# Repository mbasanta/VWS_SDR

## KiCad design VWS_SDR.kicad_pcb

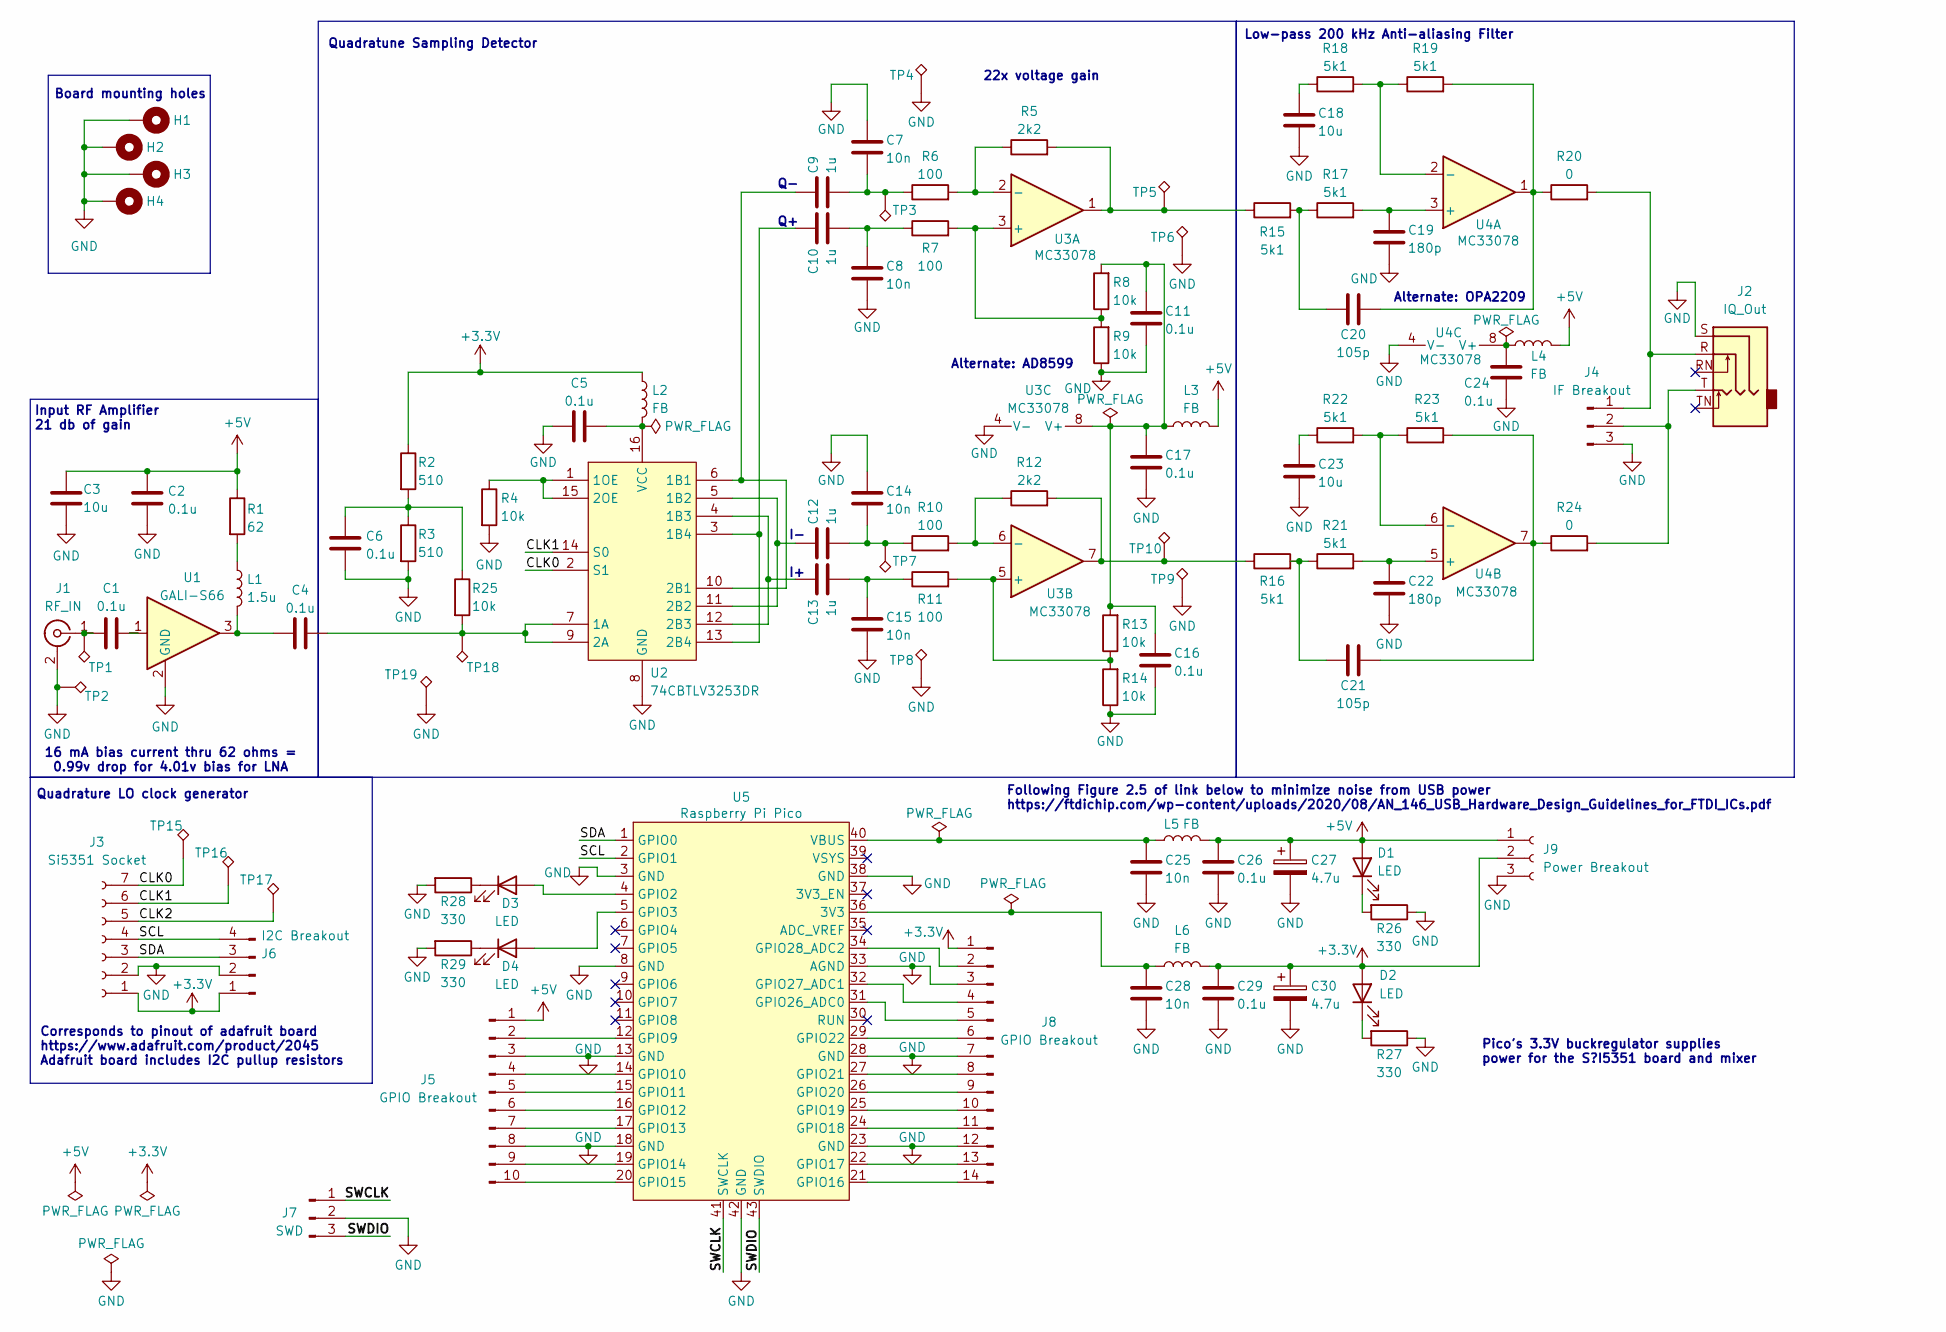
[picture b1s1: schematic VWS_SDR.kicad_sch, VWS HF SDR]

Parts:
C1, C2, C4, C5, C6, C11, C16, C17, C24, C26, C29: 0.1u; C_1206_3216Metric_Pad1.33x1.80mm_HandSolder; Digikey PN 399-C1206C104K5RACTUCT-ND
C3, C18, C23: 10u; C_1206_3216Metric_Pad1.33x1.80mm_HandSolder; Digikey PN 399-C1206C106K4RACTUCT-ND
C7, C8, C14, C15, C25, C28: 10n; C_1206_3216Metric_Pad1.33x1.80mm_HandSolder; Digikey PN 399-C1206C103K5RACTUCT-ND
C9, C10, C12, C13: 1u; C_1206_3216Metric_Pad1.33x1.80mm_HandSolder; Digikey PN 399-C1206C105K3RACTUCT-ND
C19, C22: 180p; C_1206_3216Metric_Pad1.33x1.80mm_HandSolder; Digikey PN 311-4412-1-ND
C20, C21: 105p; C_1206_3216Metric_Pad1.33x1.80mm_HandSolder; Digikey PN 399-17651-1-ND
C27, C30: 4.7u; CP_Radial_D5.0mm_P2.00mm; Digikey PN 399-ESW475M025AC3AA-ND
D1, D2: LED; LED_1206_3216Metric_Pad1.42x1.75mm_HandSolder; Digikey PN 732-4988-1-ND
D3: LED; LED_1206_3216Metric_Pad1.42x1.75mm_HandSolder; Digikey PN 732-4990-1-ND
D4: LED; LED_1206_3216Metric_Pad1.42x1.75mm_HandSolder; Digikey PN 732-4989-1-ND
H1, H2, H3, H4: MountingHole_Pad; MountingHole_3.2mm_M3_ISO7380_Pad
J1: RF_IN; SMA_Amphenol_901-144_Vertical; Digikey PN 2057-RF2-03E-T-00-50-G-ND
J2: IQ_Out; Jack_3.5mm_CUI_SJ1-3515N_Horizontal; Digikey PN CP1-3515N-ND
J3: Si5351 Socket; Adafruit_Si5351; Digikey PN 1528-1206-ND
J4: IF Breakout; PinHeader_1x03_P2.54mm_Vertical; Digikey PN 2057-RS1-03-G-ND
J5: GPIO Breakout; PinHeader_1x10_P2.54mm_Vertical; Digikey PN 2057-RS1-10-G-ND
J6: I2C Breakout; PinHeader_1x04_P2.54mm_Vertical; Digikey PN 2057-RS1-04-G-ND
J7: SWD; PinHeader_1x03_P2.54mm_Vertical; Digikey PN 2057-RS1-03-G-ND
J8: GPIO Breakout; PinHeader_1x14_P2.54mm_Vertical; Digikey PN 2057-RS1-14-G-ND
J9: Power Breakout; PinHeader_1x03_P2.54mm_Vertical; Digikey PN 2057-RS1-03-G-ND
L1: 1.5u; L_1206_3216Metric_Pad1.42x1.75mm_HandSolder; Digikey PN 541-ILSB1206ER1R5KCT-ND
L2, L3, L4, L5, L6: FB; L_1206_3216Metric_Pad1.42x1.75mm_HandSolder; Digikey PN 1934-1489-1-ND
R1: 62; R_1206_3216Metric_Pad1.30x1.75mm_HandSolder; Digikey PN 311-62ERCT-ND
R2, R3: 510; R_1206_3216Metric_Pad1.30x1.75mm_HandSolder; Digikey PN 311-510ERCT-ND
R4, R8, R9, R13, R14, R25: 10k; R_1206_3216Metric_Pad1.30x1.75mm_HandSolder; Digikey PN 311-10KERCT-ND
R5, R12: 2k2; R_1206_3216Metric_Pad1.30x1.75mm_HandSolder; Digikey PN 311-2.2KERCT-ND
R6, R7, R10, R11: 100; R_1206_3216Metric_Pad1.30x1.75mm_HandSolder; Digikey PN 311-100ERCT-ND
R15, R16, R17, R18, R19, R21, R22, R23: 5k1; R_1206_3216Metric_Pad1.30x1.75mm_HandSolder; Digikey PN 311-5.1KERCT-ND
R20, R24: 0; R_1206_3216Metric_Pad1.30x1.75mm_HandSolder; Digikey PN 311-0.0ERCT-ND
R26, R27, R28, R29: 330; R_1206_3216Metric_Pad1.30x1.75mm_HandSolder; Digikey PN 311-330ERCT-ND
TP1, TP2, TP3, TP4, TP5, TP6, TP7, TP8, TP9, TP10, TP15, TP16, TP17, TP18, TP19: TP1; TestPoint_THTPad_D2.0mm_Drill1.0mm
U1: GALI-S66; SOT-89-3; Digikey PN 3157-GALI-S66+CT-ND
U2: 74CBTLV3253DR; SOIC-16_3.9x9.9mm_P1.27mm; Digikey PN 296-9132-1-ND
U3, U4: MC33078; SOIC-8_3.9x4.9mm_P1.27mm; Digikey PN 497-1952-1-ND
U5: Raspberry Pi Pico; RPi_Pico_SMD_TH; Digikey PN 2648-SC0915CT-ND

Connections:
+3.3V: C29.1, C30.1, D2.2 (A), J3.1, J6.1, J8.1, J9.2, L2.1, L6.2, R2.1
+5V: C2.2, C3.2, C26.1, C27.1, D1.2 (A), J5.1, J9.1, L3.2, L4.2, L5.2, R1.1
/CLK0: J3.7, TP15.1, U2.2 (S1)
/CLK1: J3.6, TP16.1, U2.14 (S0)
/CLK2: J3.5, TP17.1
/SCL: J3.4, J6.4, U5.2 (GPIO1)
/SDA: J3.3, J6.3, U5.1 (GPIO0)
/SWCLK: J7.1, U5.41 (SWCLK)
/SWDIO: J7.3, U5.43 (SWDIO)
GND: C2.1, C3.1, C5.2, C6.2, C7.1, C8.2, C11.2, C14.1, C15.2, C16.2, C17.2, C18.2, C19.2, C22.2, C23.2, C24.2, C25.2, C26.2, C27.2, C28.2, C29.2, C30.2, H1.1, H2.1, H3.1, H4.1, J1.2 (Ext), J2.S, J3.2, J4.3, J5.3, J5.8, J6.2, J7.2, J8.3, J8.7, J8.12, J9.3, R3.2, R4.2, R9.1, R14.1, R26.1, R27.1, R28.2, R29.2, TP2.1, TP4.1, TP6.1, TP8.1, TP9.1, TP19.1, U1.2 (GND), U2.8 (GND), U3.4 (V-), U4.4 (V-), U5.3 (GND), U5.8 (GND), U5.13 (GND), U5.18 (GND), U5.23 (GND), U5.28 (GND), U5.33 (AGND), U5.38 (GND), U5.42 (GND)
unnamed: C1.2, U1.1
unnamed: C4.2, L1.2, U1.3
unnamed: C6.1, R2.2, R3.1, R25.1
unnamed: C7.2, C9.2, R6.1, TP3.1
unnamed: C8.1, C10.2, R7.1
unnamed: C12.2, C14.2, R10.1, TP7.1
unnamed: C13.2, C15.1, R11.1
unnamed: C18.1, R18.1
unnamed: C20.1, R19.2, R20.1, U4.1
unnamed: C20.2, R15.2, R17.1
unnamed: C21.1, R23.2, R24.1, U4.7
unnamed: C21.2, R16.2, R21.1
unnamed: C23.1, R22.1
unnamed: D1.1 (K), R26.2
unnamed: D2.1 (K), R27.2
unnamed: D3.2 (A), U5.4 (GPIO2)
unnamed: D3.1 (K), R28.1
unnamed: D4.2 (A), U5.5 (GPIO3)
unnamed: D4.1 (K), R29.1
unnamed: C1.1, J1.1 (In), TP1.1
unnamed: J2.R, J4.1, R20.2
unnamed: J2.T, J4.2, R24.2
unnamed: J5.2, U5.12 (GPIO9)
unnamed: J5.4, U5.14 (GPIO10)
unnamed: J5.5, U5.15 (GPIO11)
unnamed: J5.6, U5.16 (GPIO12)
unnamed: J5.7, U5.17 (GPIO13)
unnamed: J5.9, U5.19 (GPIO14)
unnamed: J5.10, U5.20 (GPIO15)
unnamed: J8.2, U5.34 (GPIO28_ADC2)
unnamed: J8.4, U5.32 (GPIO27_ADC1)
unnamed: J8.5, U5.31 (GPIO26_ADC0)
unnamed: J8.6, U5.29 (GPIO22)
unnamed: J8.8, U5.27 (GPIO21)
unnamed: J8.9, U5.26 (GPIO20)
unnamed: J8.10, U5.25 (GPIO19)
unnamed: J8.11, U5.24 (GPIO18)
unnamed: J8.13, U5.22 (GPIO17)
unnamed: J8.14, U5.21 (GPIO16)
unnamed: L1.1, R1.2
unnamed: R12.2, R16.1, TP10.1, U3.7
unnamed: R5.2, R15.1, TP5.1, U3.1
unnamed: C4.1, R25.2, TP18.1, U2.7 (1A), U2.9 (2A)
unnamed: C9.1, U2.6 (1B1), U2.10 (2B1)
unnamed: C12.1, U2.5 (1B2), U2.11 (2B2)
unnamed: C13.1, U2.4 (1B3), U2.12 (2B3)
unnamed: C10.1, U2.3 (1B4), U2.13 (2B4)
unnamed: R4.1, U2.1 (1OE), U2.15 (2OE)
unnamed: C5.1, L2.2, U2.16 (VCC)
unnamed: R7.2, R8.1, R9.2, U3.3 (+)
unnamed: R5.1, R6.2, U3.2 (-)
unnamed: R11.2, R13.1, R14.2, U3.5 (+)
unnamed: R10.2, R12.1, U3.6 (-)
unnamed: C11.1, C16.1, C17.1, L3.1, R8.2, R13.2, U3.8 (V+)
unnamed: C19.1, R17.2, U4.3 (+)
unnamed: R18.2, R19.1, U4.2 (-)
unnamed: C22.1, R21.2, U4.5 (+)
unnamed: R22.2, R23.1, U4.6 (-)
unnamed: C24.1, L4.1, U4.8 (V+)
unnamed: C28.1, L6.1, U5.36 (3V3)
unnamed: C25.1, L5.1, U5.40 (VBUS)

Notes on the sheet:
Alternate: OPA2209
Following Figure 2.5 of link below to minimize noise from USB power https://ftdichip.com/wp-content/uploads/2020/08/AN_146_USB_Hardware_Design_Guidelines_for_FTDI_ICs.pdf
Input RF Amplifier 21 db of gain
22x voltage gain
Corresponds to pinout of adafruit board https://www.adafruit.com/product/2045 Adafruit board includes I2C pullup resistors
16 mA bias current thru 62 ohms = 0.99v drop for 4.01v bias for LNA
Quadratune Sampling Detector
Quadrature LO clock generator
Alternate: AD8599
Pico's 3.3V buckregulator supplies power for the S?I5351 board and mixer
Board mounting holes
Low-pass 200 kHz Anti-aliasing Filter

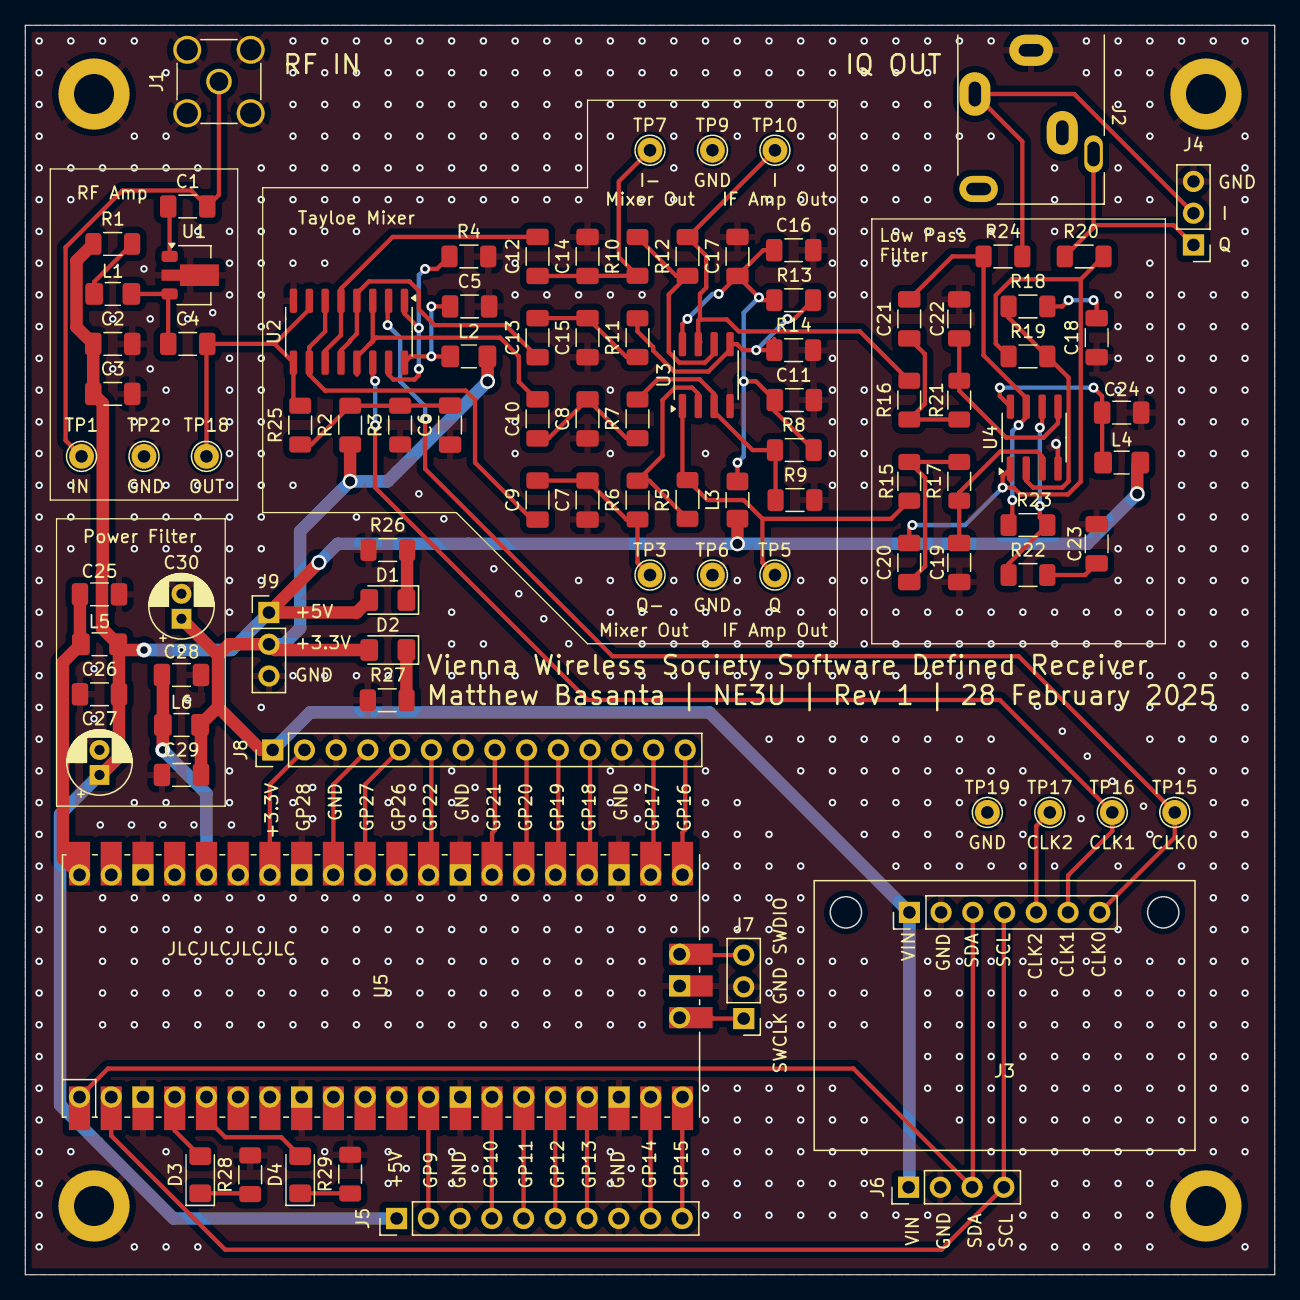
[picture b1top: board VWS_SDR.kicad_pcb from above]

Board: 4 copper layers, 99.9 x 99.9 mm, 100 parts (0 on the bottom side), 71 nets.

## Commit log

2025-03-12 Update pins used on pico
